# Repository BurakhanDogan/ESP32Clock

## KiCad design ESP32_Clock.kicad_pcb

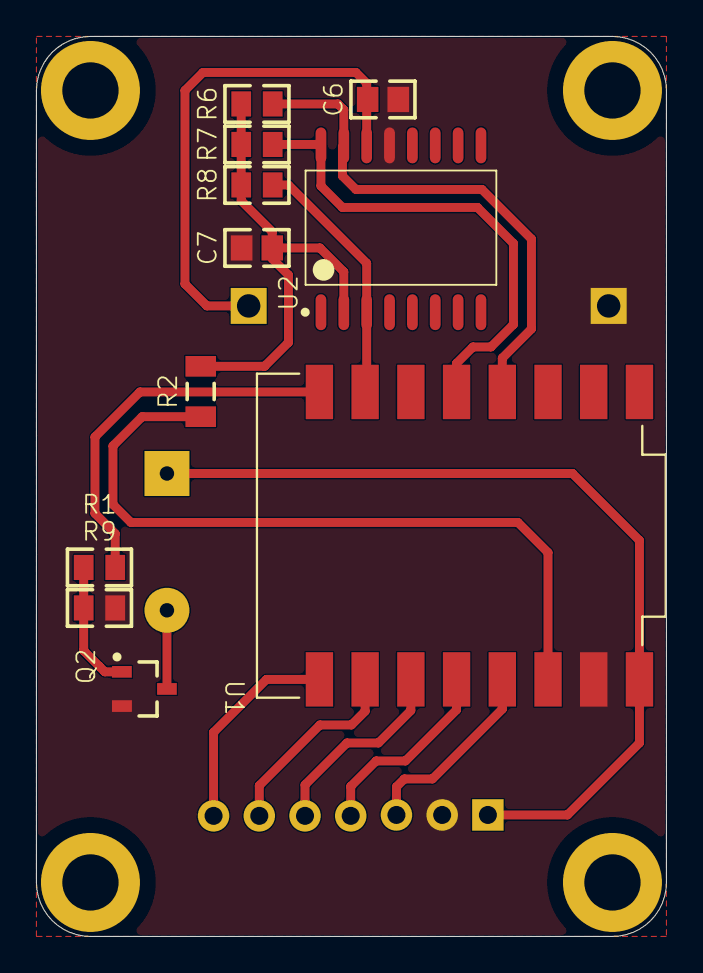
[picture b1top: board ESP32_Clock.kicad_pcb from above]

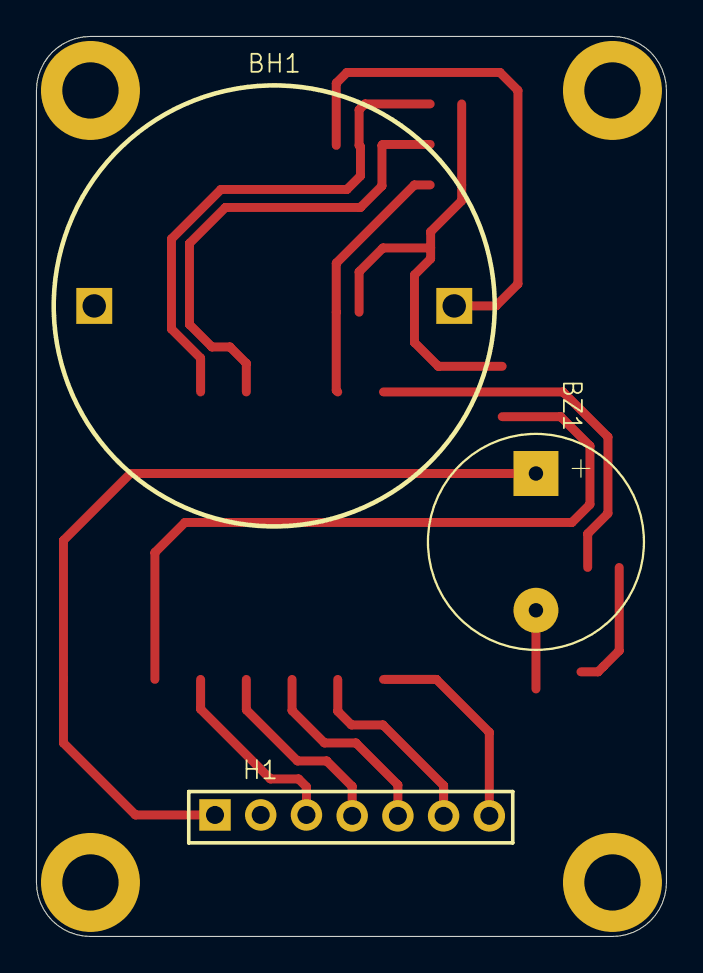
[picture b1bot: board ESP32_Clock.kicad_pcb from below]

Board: 2 copper layers, 35.0 x 50.0 mm, 14 parts (3 on the bottom side), 16 nets.

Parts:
BH1: DS1092-04-B6P; CR2032 HOLDER
BZ1: Buzzer
C6, C7: CL21B104KCFNNNE; CAPC2012X09N
H1: Header; HEADER_7PIN_2.54MM_90C
Q2: BC817-40,215; SOT23
R1: 0805S8F1001T5E; RESC2013X06N
R2: CQ06S4F0000T5E; RESC3116X06N
R6, R7, R8, R9: 0805S8F1002T5E; RESC2013X06N
U1: ESP32_C3; ESP32_C3_Mini
U2: DS3231SN# RTC; SO-16

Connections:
+3.3V: C7.2, R2.2, R6.2, R7.2, R8.2, U2.2 (Vcc)
+3.3V_ESP: R2.1, U1.3.3 (3V3)
+5V: BZ1.1 (+), H1.1, U1.5V
/BUZZER: R1.1, U1.21 (GPIO21)
/LED: H1.5, U1.2 (GPIO2)
/MCU_INT: R8.1, U1.20 (GPIO20), U2.3 (INT)
/MCU_SCL: R7.1, U1.9 (GPIO9), U2.16 (SCL)
/MCU_SDA: R6.1, U1.8 (GPIO8), U2.15 (SDA)
/SR_CLK: H1.7, U1.0 (GPIO0)
/SR_DATA: H1.3, U1.4 (GPIO4)
/SR_LATCH: H1.4, U1.3 (GPIO3)
/SR_OE: H1.6, U1.1 (GPIO1)
GND: BH1.1, C6.1, C7.1, H1.2, Q2.2 (Emiter), R9.1, U1.G (GND), U2.13 (GND)
unnamed: BZ1.2 (-), Q2.3 (Collector)
unnamed: Q2.1 (Base), R1.2, R9.2
VBAT: BH1.2, C6.2, U2.14 (VBAT)
